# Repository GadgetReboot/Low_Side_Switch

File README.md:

# Low Side Switch
16 channel low-side switch for driving resistive/inductive loads<br><br>
<br><br>
[PCBs are available at PCBWay.com][pcbway] <br><br>
This project is intended for use in a hobby electronics project environment, eg. a controlled research and development work shop to assist in the design and test of various other projects, ideas, and concepts.

It is not intended to be used as a stand alone or complete/refined product.

This design may be refined on an ongoing basis as needed, including design corrections or changes to fit or function.

If used in a situation where safety or other regulatory approval is required, it is the responsibility of the user of this design to ensure all applicable laws and regulations are followed.<br><br>

Shield: [![CC BY-SA 4.0][cc-by-sa-shield]][cc-by-sa]

This work is licensed under a
[Creative Commons Attribution-ShareAlike 4.0 International License][cc-by-sa].

[![CC BY-SA 4.0][cc-by-sa-image]][cc-by-sa]

[cc-by-sa]: http://creativecommons.org/licenses/by-sa/4.0/
[cc-by-sa-image]: https://licensebuttons.net/l/by-sa/4.0/88x31.png
[cc-by-sa-shield]: https://img.shields.io/badge/License-CC%20BY--SA%204.0-lightgrey.svg
[pcbway]: https://www.pcbway.com/project/shareproject/16_Channel_Low_Side_Switch_Driver_fce9e224.html

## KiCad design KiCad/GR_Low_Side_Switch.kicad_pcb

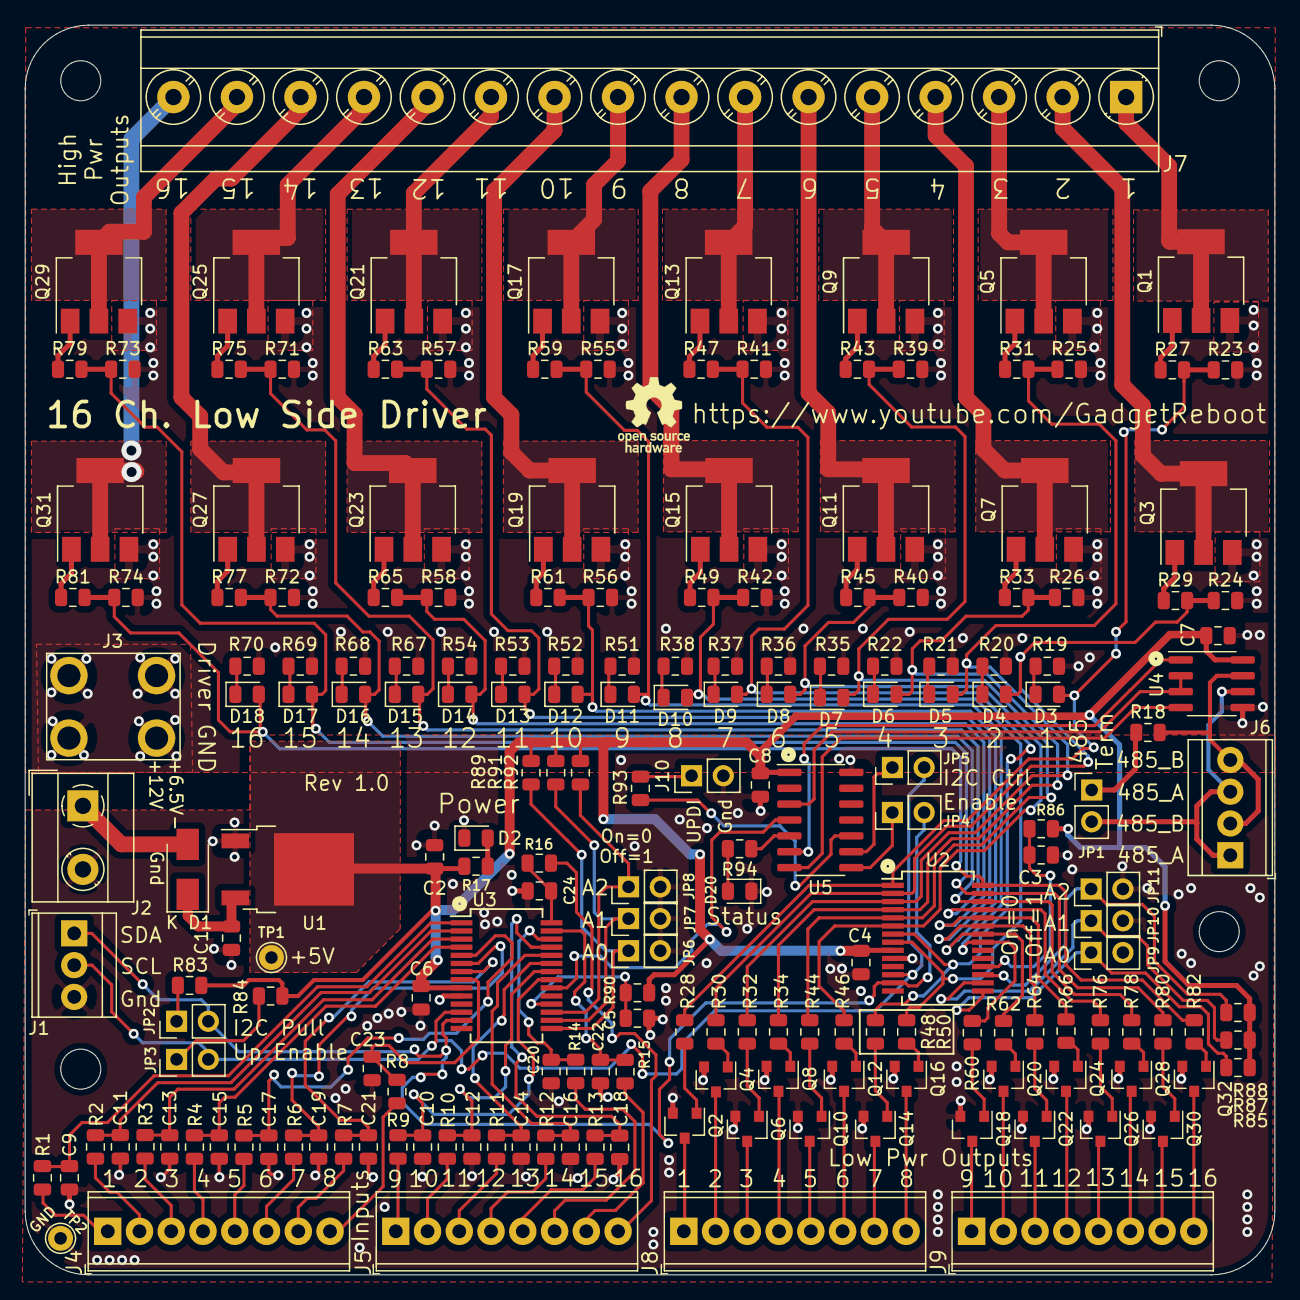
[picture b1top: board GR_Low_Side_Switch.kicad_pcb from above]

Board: 2 copper layers, 99.9 x 100.0 mm, 201 parts (0 on the bottom side), 158 nets.

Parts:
C1, C2: 10uF; C_0805_2012Metric
C3, C4, C5, C6, C7, C8, C9, C10, C11, C12, C13, C14, C15, C16, C17, C18, C19, C20, C21, C22, C23, C24: 100nF; C_0805_2012Metric
D1: SS26SHE3_B/H; D_SMA
D2: Power; LED_0805_2012Metric
D3, D4, D5, D6, D7, D8, D9, D10, D11, D12, D13, D14, D15, D16, D17, D18: LED; LED_0805_2012Metric
D20: Status; LED_0805_2012Metric
J1: Screw_Terminal_01x03; TerminalBlock_TE_282834-3_1x03_P2.54mm_Horizontal
J2: Screw_Terminal_01x02; TerminalBlock_MetzConnect_Type101_RT01602HBWC_1x02_P5.08mm_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
J3: Screw_Terminal_01x01; 7691-SEMS
J4, J5, J8, J9: Screw_Terminal_01x08; TerminalBlock_Phoenix_MPT-0,5-8-2.54_1x08_P2.54mm_Horizontal
J6: Screw_Terminal_01x04; TerminalBlock_TE_282834-4_1x04_P2.54mm_Horizontal
J7: Screw_Terminal_01x16; TerminalBlock_Phoenix_MKDS-3-16-5.08_1x16_P5.08mm_Horizontal
J10: Conn_01x02; PinHeader_1x02_P2.54mm_Vertical
JP1, JP2, JP3, JP4, JP5, JP6, JP7, JP8, JP9, JP10, JP11: Conn_01x02; PinHeader_1x02_P2.54mm_Vertical
MH1, MH2, MH3, MH4: MountingHole; MountingHole_3.2mm_M3
Q1, Q3, Q5, Q7, Q9, Q11, Q13, Q15, Q17, Q19, Q21, Q23, Q25, Q27, Q29, Q31: BUK98150-55A; SOT-223-3_TabPin2
Q2, Q4, Q6, Q8, Q10, Q12, Q14, Q16, Q18, Q20, Q22, Q24, Q26, Q28, Q30, Q32: MMBT3904; SOT-23
R1, R2, R3, R4, R5, R6, R7, R8, R9, R10, R11, R12, R13, R14, R15, R16, R19, R20, R21, R22, R27, R29, R31, R33, R35, R36, R37, R38, R43, R45, R47, R49, R51, R52, R53, R54, R59, R61, R63, R65, R67, R68, R69, R70, R75, R77, R79, R81, R93: 1K5; R_0805_2012Metric
R17, R94: 4K7; R_0805_2012Metric
R18: 120r; R_0805_2012Metric
R23, R24, R25, R26, R39, R40, R41, R42, R55, R56, R57, R58, R71, R72, R73, R74, R83, R84, R85, R86, R87, R88, R89, R90, R91, R92: 10K; R_0805_2012Metric
R28, R30, R32, R34, R44, R46, R48, R50, R60, R62, R64, R66, R76, R78, R80, R82: 15K; R_0805_2012Metric
TP1, TP2: TestPoint_Alt; TestPoint_THTPad_D2.0mm_Drill1.0mm
U1: NCP1117-5.0; TO-252-2
U2, U3: MCP23017_SS; SSOP-28_5.3x10.2mm_P0.65mm_modified
U4: MAX485; SOIC-8_3.9x4.9mm_P1.27mm
U5: ATtiny x04/x14; SOIC-14_3.9x8.7mm_P1.27mm

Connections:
/485_A: J6.1, J6.3, JP1.2, U4.6
/485_B: J6.2, J6.4, R18.2, U4.7
/Driver 1-16/Ctrl1: D3.2, R23.1, R27.2, R28.2, U2.1
/Driver 1-16/Ctrl2: D4.2, R24.1, R29.2, R30.2, U2.2
/Driver 1-16/Ctrl3: D5.2, R25.1, R31.2, R32.2, U2.3
/Driver 1-16/Ctrl4: D6.2, R26.1, R33.2, R34.2, U2.4
/Driver 1-16/Ctrl5: D7.2, R39.1, R43.2, R44.2, U2.5
/Driver 1-16/Ctrl6: D8.2, R40.1, R45.2, R46.2, U2.6
/Driver 1-16/Ctrl7: D9.2, R41.1, R47.2, R48.2, U2.7
/Driver 1-16/Ctrl8: D10.2, R42.1, R49.2, R50.2, U2.8
/Driver 1-16/Ctrl9: D11.2, R55.1, R59.2, R60.2, U2.21
/Driver 1-16/Ctrl10: D12.2, R56.1, R61.2, R62.2, U2.22
/Driver 1-16/Ctrl11: D13.2, R57.1, R63.2, R64.2, U2.23
/Driver 1-16/Ctrl12: D14.2, R58.1, R65.2, R66.2, U2.24
/Driver 1-16/Ctrl13: D15.2, R71.1, R75.2, R76.2, U2.25
/Driver 1-16/Ctrl14: D16.2, R72.1, R77.2, R78.2, U2.26
/Driver 1-16/Ctrl15: D17.2, R73.1, R79.2, R80.2, U2.27
/Driver 1-16/Ctrl16: D18.2, R74.1, R81.2, R82.2, U2.28
/Drv1a: J7.1, Q1.2
/Drv1b: J8.1, Q2.3
/Drv2a: J7.2, Q3.2
/Drv2b: J8.2, Q4.3
/Drv3a: J7.3, Q5.2
/Drv3b: J8.3, Q6.3
/Drv4a: J7.4, Q7.2
/Drv4b: J8.4, Q8.3
/Drv5a: J7.5, Q9.2
/Drv5b: J8.5, Q10.3
/Drv6a: J7.6, Q11.2
/Drv6b: J8.6, Q12.3
/Drv7a: J7.7, Q13.2
/Drv7b: J8.7, Q14.3
/Drv8a: J7.8, Q15.2
/Drv8b: J8.8, Q16.3
/Drv9a: J7.9, Q17.2
/Drv9b: J9.1, Q18.3
/Drv10a: J7.10, Q19.2
/Drv10b: J9.2, Q20.3
/Drv11a: J7.11, Q21.2
/Drv11b: J9.3, Q22.3
/Drv12a: J7.12, Q23.2
/Drv12b: J9.4, Q24.3
/Drv13a: J7.13, Q25.2
/Drv13b: J9.5, Q26.3
/Drv14a: J7.14, Q27.2
/Drv14b: J9.6, Q28.3
/Drv15a: J7.15, Q29.2
/Drv15b: J9.7, Q30.3
/Drv16a: J7.16, Q31.2
/Drv16b: J9.8, Q32.3
/GPIO Expander/Inp1: C9.2, R1.1, U3.1
/GPIO Expander/Inp2: C11.2, R2.1, U3.2
/GPIO Expander/Inp3: C13.2, R3.1, U3.3
/GPIO Expander/Inp4: C15.2, R4.1, U3.4
/GPIO Expander/Inp5: C17.2, R5.1, U3.5
/GPIO Expander/Inp6: C19.2, R6.1, U3.6
/GPIO Expander/Inp7: C21.2, R7.1, U3.7
/GPIO Expander/Inp8: C23.2, R8.1, U3.8
/GPIO Expander/Inp9: C10.2, R9.1, U3.21
/GPIO Expander/Inp10: C12.2, R10.1, U3.22
/GPIO Expander/Inp11: C14.2, R11.1, U3.23
/GPIO Expander/Inp12: C16.2, R12.1, U3.24
/GPIO Expander/Inp13: C18.2, R13.1, U3.25
/GPIO Expander/Inp14: C20.2, R14.1, U3.26
/GPIO Expander/Inp15: C22.2, R15.1, U3.27
/GPIO Expander/Inp16: C24.2, R16.1, U3.28
/I2C_Controller/DE_~RE: U4.2, U4.3, U5.3
/I2C_Controller/PA7: R94.1, U5.5
/I2C_Controller/RX_In: U4.1, U5.6
/I2C_Controller/SCLint: JP5.1, U5.9
/I2C_Controller/SDAint: JP4.1, U5.8
/I2C_Controller/TX_Out: U4.4, U5.7
/I2C_Controller/UPDI: R93.2, U5.10
/INTA: U3.20, U5.4
/Input1: J4.1, R1.2
/Input2: J4.2, R2.2
/Input3: J4.3, R3.2
/Input4: J4.4, R4.2
/Input5: J4.5, R5.2
/Input6: J4.6, R6.2
/Input7: J4.7, R7.2
/Input8: J4.8, R8.2
/Input9: J5.1, R9.2
/Input10: J5.2, R10.2
/Input11: J5.3, R11.2
/Input12: J5.4, R12.2
/Input13: J5.5, R13.2
/Input14: J5.6, R14.2
/Input15: J5.7, R15.2
/Input16: J5.8, R16.2
/SCL: J1.2, JP3.2, JP5.2, U2.12, U3.12
/SDA: J1.1, JP2.2, JP4.2, U2.13, U3.13
GNDREF: C1.1, C2.1, C3.1, C4.2, C5.1, C6.2, C7.2, C8.2, C9.1, C10.1, C11.1, C12.1, C13.1, C14.1, C15.1, C16.1, C17.1, C18.1, C19.1, C20.1, C21.1, C22.1, C23.1, C24.1, D2.1, D20.1, J1.3, J2.2, J3.1, J10.2, JP6.2, JP7.2, JP8.2, JP9.2, JP10.2, JP11.2, Q1.3, Q2.2, Q3.3, Q4.2, Q5.3, Q6.2, Q7.3, Q8.2, Q9.3, Q10.2, Q11.3, Q12.2, Q13.3, Q14.2, Q15.3, Q16.2, Q17.3, Q18.2, Q19.3, Q20.2, Q21.3, Q22.2, Q23.3, Q24.2, Q25.3, Q26.2, Q27.3, Q28.2, Q29.3, Q30.2, Q31.3, Q32.2, R19.2, R20.2, R21.2, R22.2, R23.2, R24.2, R25.2, R26.2, R35.2, R36.2, R37.2, R38.2, R39.2, R40.2, R41.2, R42.2, R51.2, R52.2, R53.2, R54.2, R55.2, R56.2, R57.2, R58.2, R67.2, R68.2, R69.2, R70.2, R71.2, R72.2, R73.2, R74.2, TP2.1, U1.1, U2.10, U3.10, U4.5, U5.14
unnamed: C1.2, D1.1, U1.3
unnamed: C3.2, R86.2, U2.18
unnamed: C5.2, R90.2, U3.18
unnamed: D1.2, J2.1
unnamed: D2.2, R17.2
unnamed: D3.1, R19.1
unnamed: D4.1, R20.1
unnamed: D5.1, R21.1
unnamed: D6.1, R22.1
unnamed: D7.1, R35.1
unnamed: D8.1, R36.1
unnamed: D9.1, R37.1
unnamed: D10.1, R38.1
unnamed: D11.1, R51.1
unnamed: D12.1, R52.1
unnamed: D13.1, R53.1
unnamed: D14.1, R54.1
unnamed: D15.1, R67.1
unnamed: D16.1, R68.1
unnamed: D17.1, R69.1
unnamed: D18.1, R70.1
unnamed: D20.2, R94.2
unnamed: J10.1, R93.1
unnamed: JP1.1, R18.1
unnamed: JP2.1, R83.2
unnamed: JP3.1, R84.2
unnamed: JP6.1, R89.2, U3.15
unnamed: JP7.1, R91.2, U3.16
unnamed: JP8.1, R92.2, U3.17
unnamed: JP9.1, R85.2, U2.15
unnamed: JP10.1, R87.2, U2.16
unnamed: JP11.1, R88.2, U2.17
unnamed: Q1.1, R27.1
unnamed: Q2.1, R28.1
unnamed: Q3.1, R29.1
unnamed: Q4.1, R30.1
unnamed: Q5.1, R31.1
unnamed: Q6.1, R32.1
unnamed: Q7.1, R33.1
unnamed: Q8.1, R34.1
unnamed: Q9.1, R43.1
unnamed: Q10.1, R44.1
unnamed: Q11.1, R45.1
unnamed: Q12.1, R46.1
unnamed: Q13.1, R47.1
unnamed: Q14.1, R48.1
unnamed: Q15.1, R49.1
unnamed: Q16.1, R50.1
unnamed: Q17.1, R59.1
unnamed: Q18.1, R60.1
unnamed: Q19.1, R61.1
unnamed: Q20.1, R62.1
unnamed: Q21.1, R63.1
unnamed: Q22.1, R64.1
unnamed: Q23.1, R65.1
unnamed: Q24.1, R66.1
unnamed: Q25.1, R75.1
unnamed: Q26.1, R76.1
unnamed: Q27.1, R77.1
unnamed: Q28.1, R78.1
unnamed: Q29.1, R79.1
unnamed: Q30.1, R80.1
unnamed: Q31.1, R81.1
unnamed: Q32.1, R82.1
VCC: C2.2, C4.1, C6.1, C7.1, C8.1, R17.1, R83.1, R84.1, R85.1, R86.1, R87.1, R88.1, R89.1, R90.1, R91.1, R92.1, TP1.1, U1.2, U2.9, U3.9, U4.8, U5.1

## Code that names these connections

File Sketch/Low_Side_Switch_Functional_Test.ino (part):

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
// the mcp23017 that is connected as pcb inputs has an interrupt output
// connecting to ATTiny input PA6 (pin 2 in Arduino)
#define INTA_PIN 2

// map pcb inputs and outputs to MCP23017 Arduino mapped pin numbers
// the banks of 8 gpio are not assigned one to one with
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
// pcb inputs are connected to mcp23017 at address "inputsAddr"

#define input1    8   // GPB0 input
#define input2    9   // GPB1 input
#define input3    10  // GPB2 input
#define input4    11  // GPB3 input
#define input5    12  // GPB4 input
#define input6    13  // GPB5 input
#define input7    14  // GPB6 input
#define input8    15  // GPB7 input

#define input9     0   // GPA0 input
#define input10    1   // GPA1 input
#define input11    2   // GPA2 input
#define input12    3   // GPA3 input
#define input13    4   // GPA4 input
#define input14    5   // GPA5 input
#define input15    6   // GPA6 input
#define input16    7   // GPA7 input

// pcb outputs are connected to mcp23017 at address "outputsAddr"

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#define output15    6   // GPA6 output
#define output16    7   // GPA7 output

#define statusLED 3                    // pcb "status" LED is on ATTiny PA7 (pin 3 on Arduino)

volatile boolean intOccurred = false;  // flag if an interrupt has occurred on pcb input pins

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  digitalWrite(statusLED, 0);

  // configure input pins as inputs with pull up
  gpioInputs.pinMode(input1, INPUT_PULLUP);
  gpioInputs.pinMode(input2, INPUT_PULLUP);
  gpioInputs.pinMode(input3, INPUT_PULLUP);
  gpioInputs.pinMode(input4, INPUT_PULLUP);
  gpioInputs.pinMode(input5, INPUT_PULLUP);
  gpioInputs.pinMode(input6, INPUT_PULLUP);
  gpioInputs.pinMode(input7, INPUT_PULLUP);
  gpioInputs.pinMode(input8, INPUT_PULLUP);
  gpioInputs.pinMode(input9, INPUT_PULLUP);
  gpioInputs.pinMode(input10, INPUT_PULLUP);
  gpioInputs.pinMode(input11, INPUT_PULLUP);
  gpioInputs.pinMode(input12, INPUT_PULLUP);
  gpioInputs.pinMode(input13, INPUT_PULLUP);
  gpioInputs.pinMode(input14, INPUT_PULLUP);
  gpioInputs.pinMode(input15, INPUT_PULLUP);
  gpioInputs.pinMode(input16, INPUT_PULLUP);

  // configure output pins as outputs
  gpioOutputs.pinMode(output1, OUTPUT);
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  gpioOutputs.writeGPIO(0x00, 0);  // port A (outputs 9..16) write 0x00
  gpioOutputs.writeGPIO(0x00, 1);  // port B (outputs 1..8)  write 0x00

  // configure ATTiny pin that will read mcp23017 interrupt INTA/B state
  pinMode(INTA_PIN, INPUT_PULLUP);

  // OPTIONAL - call this to override defaults
  // mirror INTA/B so only one wire required
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  //        not sure if the library is the issue or some sketch specific thing
  //        for the purposes of this sketch, interrupts are not used but may be attempted later

  gpioInputs.setupInterruptPin(input1, CHANGE);
  gpioInputs.setupInterruptPin(input2, CHANGE);
  gpioInputs.setupInterruptPin(input3, CHANGE);
  gpioInputs.setupInterruptPin(input4, CHANGE);
  gpioInputs.setupInterruptPin(input5, CHANGE);
  gpioInputs.setupInterruptPin(input6, CHANGE);
  gpioInputs.setupInterruptPin(input7, CHANGE);
  gpioInputs.setupInterruptPin(input8, CHANGE);

  attachInterrupt(digitalPinToInterrupt(INTA_PIN), mcpInputInterrupt, CHANGE);
}

void loop() {
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// read inputs and configure current run mode
void setRunMode() {

  if (!gpioInputs.digitalRead(input1)) {
    currentMode = outFollowsIn_9_16;  // outputs 9..16 are on/off based on inputs 9..16
  }

  if (!gpioInputs.digitalRead(input2)) {
    currentMode = cycleOutputs_1_16; // outputs 1..16 are momentarily turned on and off sequentially
  }

  if (!gpioInputs.digitalRead(input3)) {
    currentMode = allOutputsOnDecreasingInterval;  // turn all outputs on at once, then off, then shorten delay
  }

  if (!gpioInputs.digitalRead(input4)) {
    currentMode = allOutputsOn;  // turn all outputs on
  }

  if (!gpioInputs.digitalRead(input5)) {
    currentMode = allOutputsOff;  // turn all outputs off
  }
}
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// read inputs and make corresponding outputs follow [inverted/active low] inputs
void outputsFollowInputs() {

  gpioOutputs.digitalWrite(output9, !gpioInputs.digitalRead(input9));
  gpioOutputs.digitalWrite(output10, !gpioInputs.digitalRead(input10));
  gpioOutputs.digitalWrite(output11, !gpioInputs.digitalRead(input11));
  gpioOutputs.digitalWrite(output12, !gpioInputs.digitalRead(input12));
  gpioOutputs.digitalWrite(output13, !gpioInputs.digitalRead(input13));
  gpioOutputs.digitalWrite(output14, !gpioInputs.digitalRead(input14));
  gpioOutputs.digitalWrite(output15, !gpioInputs.digitalRead(input15));
  gpioOutputs.digitalWrite(output16, !gpioInputs.digitalRead(input16));

}

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
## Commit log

2022-09-18 Create LICENSE
